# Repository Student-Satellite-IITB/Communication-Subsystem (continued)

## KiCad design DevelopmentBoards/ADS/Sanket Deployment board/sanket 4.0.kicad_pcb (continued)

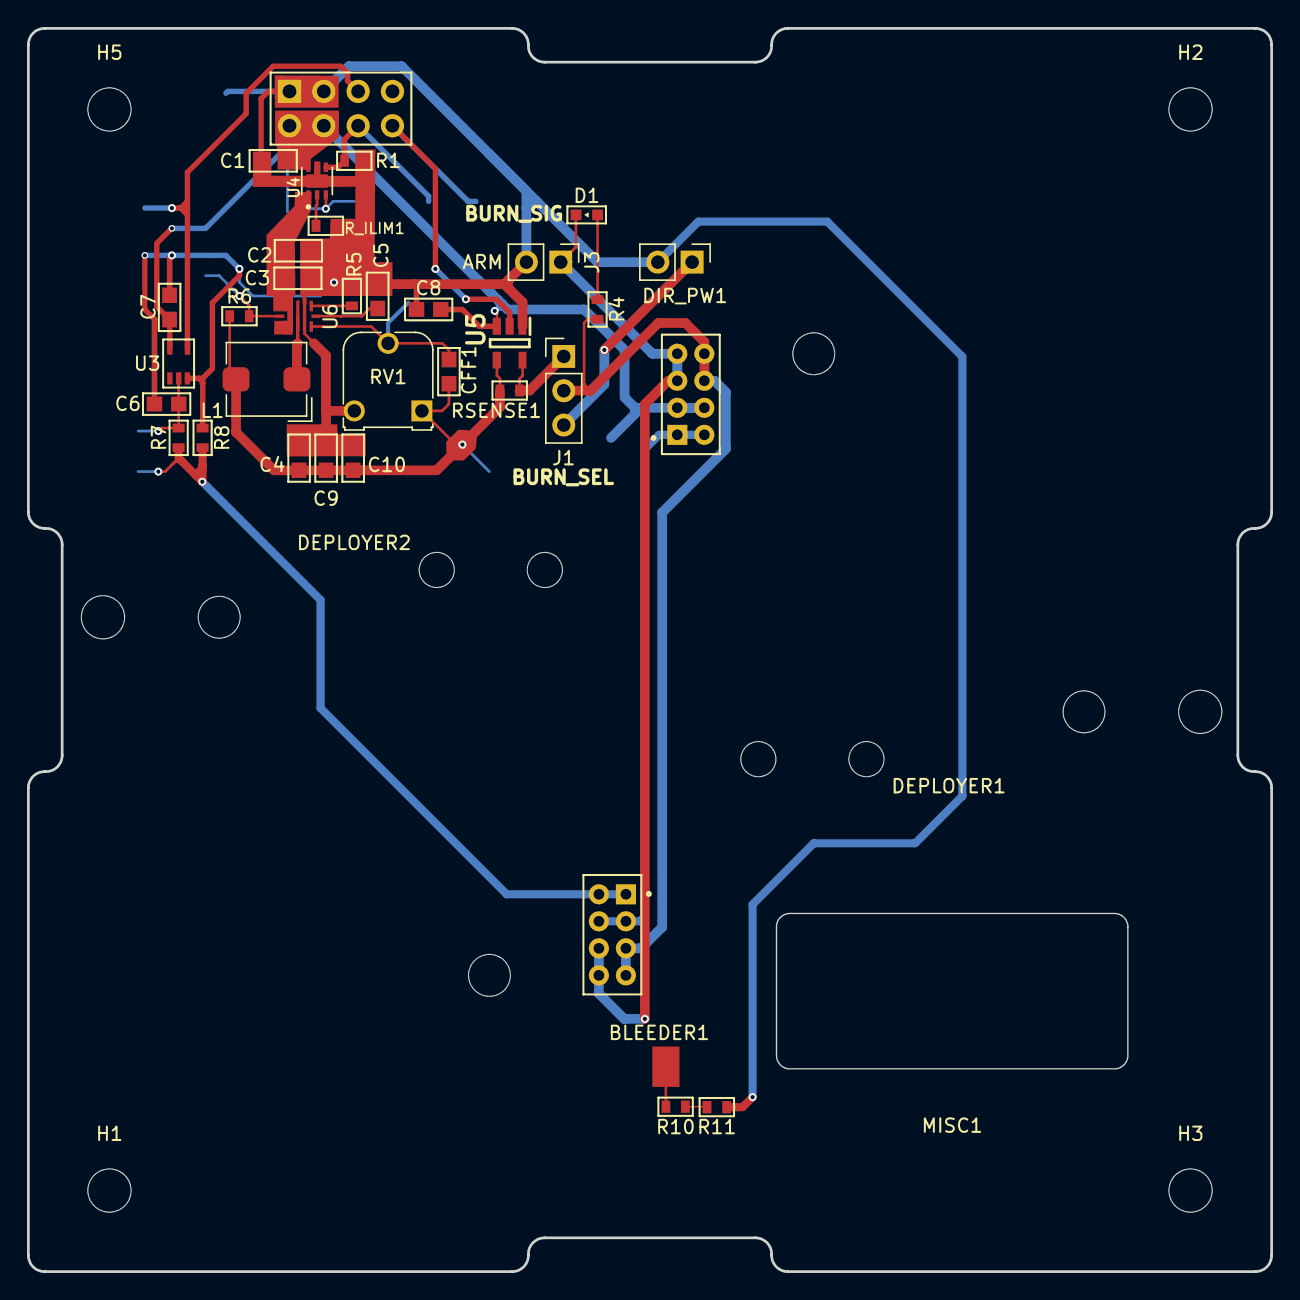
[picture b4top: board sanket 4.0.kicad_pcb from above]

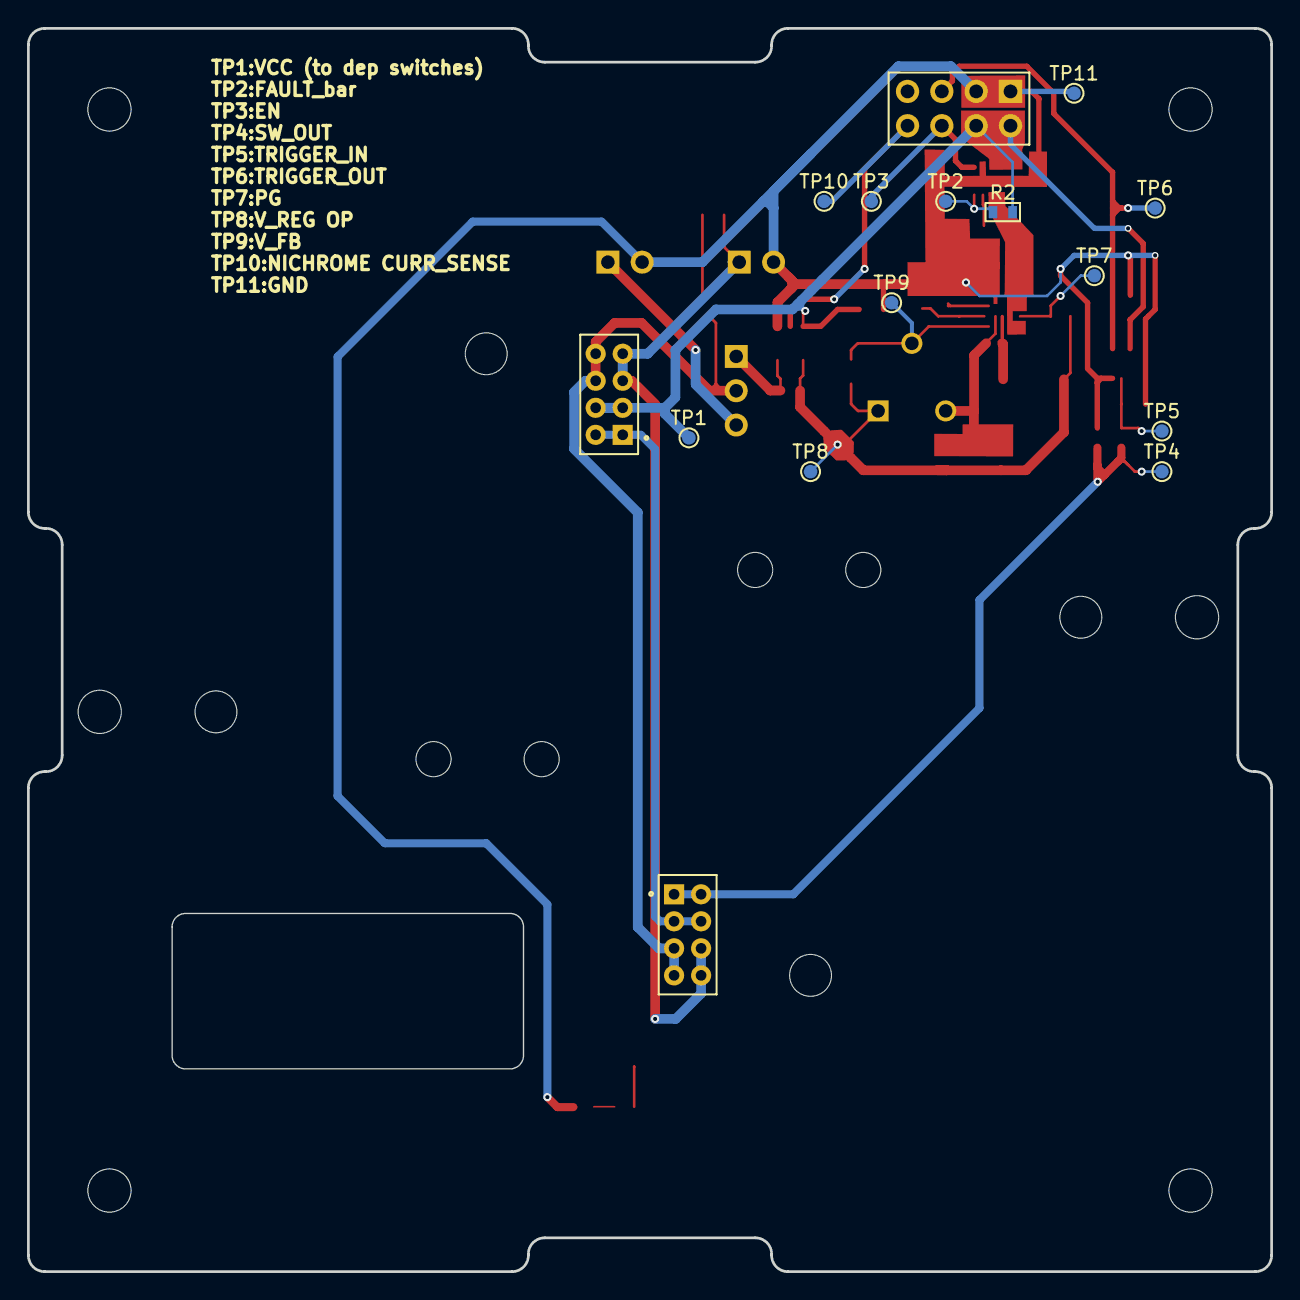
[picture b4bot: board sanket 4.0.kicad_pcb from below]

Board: 2 copper layers, 92.0 x 92.0 mm, 52 parts (12 on the bottom side), 24 nets.

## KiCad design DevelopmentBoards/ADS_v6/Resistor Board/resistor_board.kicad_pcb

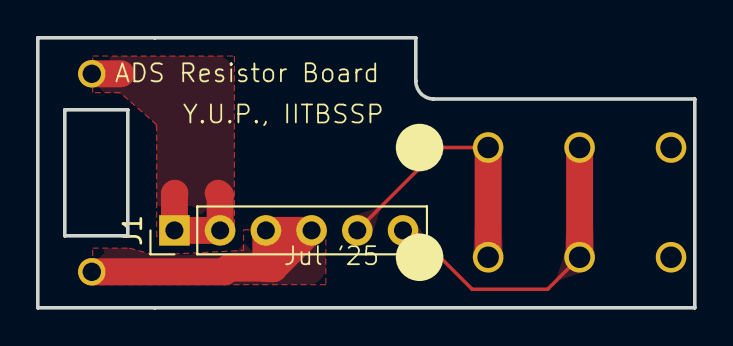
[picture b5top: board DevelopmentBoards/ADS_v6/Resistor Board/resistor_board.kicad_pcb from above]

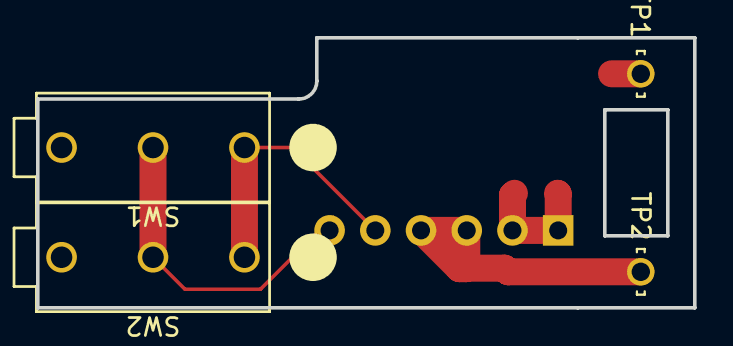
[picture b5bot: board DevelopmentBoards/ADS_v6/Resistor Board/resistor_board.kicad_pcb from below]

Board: 2 copper layers, 36.5 x 15.0 mm, 5 parts (4 on the bottom side), 4 nets.

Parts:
J1: Conn_01x06_Pin; PinHeader_1x06_P2.54mm_Vertical
SW1, SW2: SW_SPDT; D2F-L_OMR
TP1, TP2: 5021; TP_5021

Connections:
/BurnWireIN: J1.1, J1.2, TP1.TP
/DeployerDetectionSWIN: J1.5, SW1.1 (A), SW2.1 (A)
/DeployerDetectionSWOUT: J1.6, SW1.2 (B), SW2.2 (B)
/GND: J1.3, J1.4, TP2.TP

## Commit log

2025-01-12 Comm Board v2.0 Design
    started designing v2.0 of Comm board
2025-03-31 Rename ReadeMe.md to ReadMe.md
2025-03-31 add Sanket and Resistor board
2025-07-12 Add new version Move old board files to v4
2025-07-24 add sch pdf
2025-07-25 add bom
2025-07-27 add bom, update .gitignore
2025-08-24 update sch pdf
